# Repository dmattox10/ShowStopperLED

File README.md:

# ShowStopperLED
A five channel LED strip lighting Controller with serious audio reactivity and many display modes

The Android app communicates over Bluetooth 2.1 with the board, setting modes, and individual settings for each mode.
There is an audio input, which I was really impressed with myself for, because it introduced ZERO noise at all! The audio modes were my absolute favorite.

I stopped working on this project 7 years ago. I got mine working, as well as one for a friend, but a week after I got my prototypes in the mail and assembled them, the competitor released pretty much the same thing, ready for sale, and I gave up.

There are many different iterations, most untested, but the "defiance" version was built, and used successfully, including a $500 traffic ticket because I didn't realize it was on, and it was flashing "Red-Red", "Blue-Blue" on my car, and I got pulled over.

# An Apology: This was all completed and over, before I ever learned about Git!

## Android:
I've included every copy of the source code I have found in my old backups, I didn't compile and test any at this point, since I've switched to iOS personally, and don't have any Android devices lying around. I didn't use or have any apple equipment when I started the project.

## Boards:
I've included every version I made a board for, again, only "defiance" was produced in quantity and tested thoroughly.

## Arduino:
I started with an ATmega328P, moved to a PJRC Teensy 2.0, the code is a mess of files, and I can't tell which one is the "latest" version. The longest iterations are over 2k lines, pretty well commented.

## Media:
All of the files in this directory are photos of the equipment or advertising materials I came up with.

## Demo Links:
I recorded two videos with one of my best friends, of the ShowStopper working, on my 1993 Dodge Stealth.
- [Audio Modes](https://www.youtube.com/watch?v=f9GeiqDAIMo)
- [Motion Modes](https://www.youtube.com/watch?v=yMCRMerskfM)

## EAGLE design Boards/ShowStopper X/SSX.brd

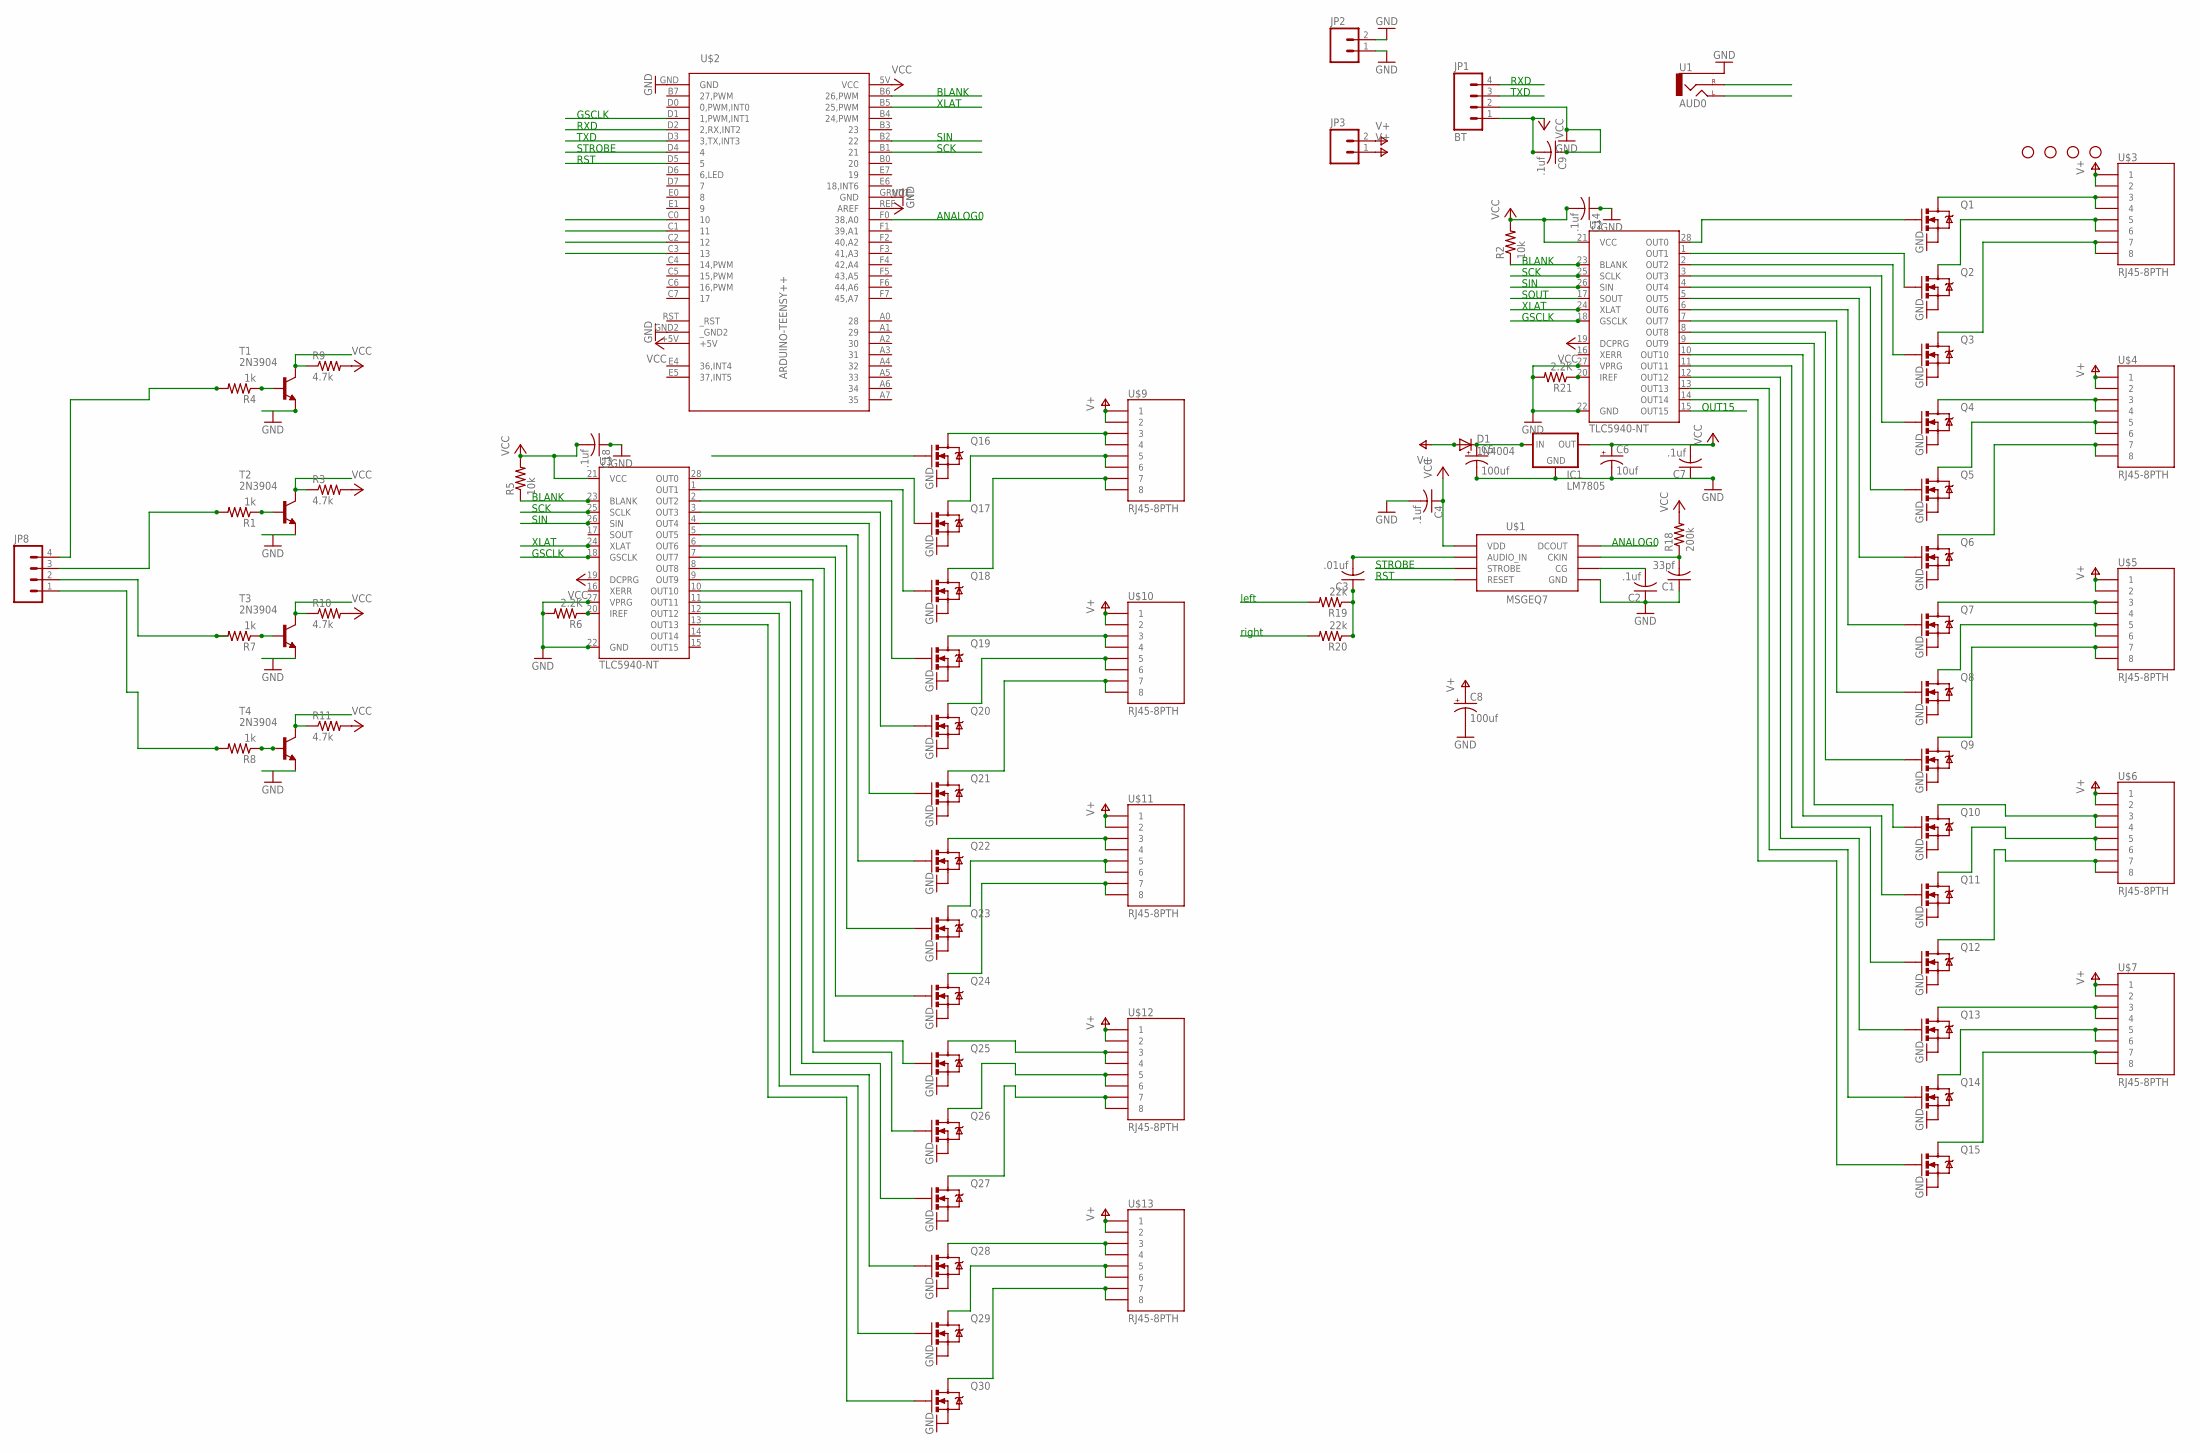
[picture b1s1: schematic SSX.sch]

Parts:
C1: 33pf; C025-025X050
C2, C4, C7, C9, C14, C18: .1uf; C025-025X050
C3: .01uf; C025-025X050
C5, C8: 100uf; CPOL-RADIAL-100UF-25V
C6: 10uf; CPOL-RADIAL-10UF-25V
D1: 1N4004; DIODE-1N4001
IC1: LM7805; TO220-IGO
JP1: BT; 1X04_LOCK
JP2, JP3: M025MM; SCREWTERMINAL-5MM-2
JP4, JP5, JP6, JP7: STAND-OFF
JP8: M04PTH; 1X04
Q1, Q2, Q3, Q4, Q5, Q6, Q7, Q8, Q9, Q10, Q11, Q12, Q13, Q14, Q15, Q16, Q17, Q18, Q19, Q20, Q21, Q22, Q23, Q24, Q25, Q26, Q27, Q28, Q29, Q30: MOSFET-NCHANNELPTH2; TO220V
R1, R4, R7, R8: 1k; 0207/2V
R2, R5: 10k; 0207/2V
R3, R9, R10, R11: 4.7k; 0207/2V
R6, R21: 2.2K; 0207/2V
R18: 200k; 0207/2V
R19, R20: 22k; 0207/2V
T1, T2, T3, T4: 2N3904; TO92
U1: AUD0; AUDIO-JACK
U2, U3: TLC5940-NT; DIL28-3
U$1: MSGEQ7_PTH; DIL08
U$2: ARDUINO-TEENSY++; TEENSY++
U$3, U$4, U$5, U$6, U$7, U$9, U$10, U$11, U$12, U$13: RJ45-8PTH; RJ45-8

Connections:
ANALOG0: U$1.3 (DCOUT), U$2.F0 (38,A0)
ARS: U$1.7 (RESET), U$2.D5 (5)
BL: R10.1, T3.1 (C), U$2.C1 (11)
BLANK: R2.1, U2.23 (BLANK), U$2.B6 (26,PWM)
BLANK1: R5.1, U3.23 (BLANK)
GND: C1.1, C2.1, C4.2, C5.2 (-), C6.2 (-), C7.1, C8.2 (-), C9.1, C14.1, C18.1, IC1.GND, JP1.2, JP2.1, JP2.2, Q1.3 (S), Q2.3 (S), Q3.3 (S), Q4.3 (S), Q5.3 (S), Q6.3 (S), Q7.3 (S), Q8.3 (S), Q9.3 (S), Q10.3 (S), Q11.3 (S), Q12.3 (S), Q13.3 (S), Q14.3 (S), Q15.3 (S), Q16.3 (S), Q17.3 (S), Q18.3 (S), Q19.3 (S), Q20.3 (S), Q21.3 (S), Q22.3 (S), Q23.3 (S), Q24.3 (S), Q25.3 (S), Q26.3 (S), Q27.3 (S), Q28.3 (S), Q29.3 (S), Q30.3 (S), R6.2, R21.2, U1.SLEEVE, U2.22 (GND), U2.27 (VPRG), U3.22 (GND), U3.27 (VPRG), U$1.2 (GND), U$2.GND, U$2.GND2 (_GND2), U$2.GRND1 (GND)
GSCLK: U2.18 (GSCLK), U$2.D1 (1,PWM,INT1)
GSCLK1: U3.18 (GSCLK)
HL: R11.1, T4.1 (C), U$2.C0 (10)
LEFT: R19.2, U1.TIP (LEFT)
LTS: R3.1, T2.1 (C), U$2.C2 (12)
unnamed: Q7.2 (D), U$5.3, U$5.4
unnamed: Q2.2 (D), U$3.5, U$3.6
unnamed: Q3.2 (D), U$3.7, U$3.8
unnamed: Q10.2 (D), U$6.3, U$6.4
unnamed: Q9.1 (G), U2.8 (OUT8)
unnamed: Q2.1 (G), U2.1 (OUT1)
unnamed: Q3.1 (G), U2.2 (OUT2)
unnamed: Q4.1 (G), U2.3 (OUT3)
unnamed: Q5.2 (D), U$4.5, U$4.6
unnamed: Q5.1 (G), U2.4 (OUT4)
unnamed: Q6.1 (G), U2.5 (OUT5)
unnamed: Q7.1 (G), U2.6 (OUT6)
unnamed: Q8.1 (G), U2.7 (OUT7)
unnamed: Q17.1 (G), U3.28 (OUT0)
unnamed: Q10.1 (G), U2.9 (OUT9)
unnamed: Q11.1 (G), U2.10 (OUT10)
unnamed: Q12.1 (G), U2.11 (OUT11)
unnamed: Q13.1 (G), U2.12 (OUT12)
unnamed: Q14.1 (G), U2.13 (OUT13)
unnamed: Q15.1 (G), U2.14 (OUT14)
unnamed: Q6.2 (D), U$4.7, U$4.8
unnamed: Q13.2 (D), U$7.3, U$7.4
unnamed: Q8.2 (D), U$5.5, U$5.6
unnamed: C1.2, R18.1, U$1.8 (CKIN)
unnamed: Q9.2 (D), U$5.7, U$5.8
unnamed: Q14.2 (D), U$7.5, U$7.6
unnamed: Q11.2 (D), U$6.5, U$6.6
unnamed: C3.2, U$1.5 (AUDIO_IN)
unnamed: Q12.2 (D), U$6.7, U$6.8
unnamed: Q15.2 (D), U$7.7, U$7.8
unnamed: Q1.2 (D), U$3.3, U$3.4
unnamed: C2.2, U$1.6 (CG)
unnamed: Q4.2 (D), U$4.3, U$4.4
unnamed: Q1.1 (G), U2.28 (OUT0)
unnamed: R21.1, U2.20 (IREF)
unnamed: C3.1, R19.1, R20.1
unnamed: Q18.1 (G), U3.1 (OUT1)
unnamed: Q19.1 (G), U3.2 (OUT2)
unnamed: Q20.1 (G), U3.3 (OUT3)
unnamed: C5.1 (+), D1.C, IC1.IN
unnamed: Q21.1 (G), U3.4 (OUT4)
unnamed: Q22.1 (G), U3.5 (OUT5)
unnamed: Q23.1 (G), U3.6 (OUT6)
unnamed: Q25.1 (G), U3.8 (OUT8)
unnamed: Q26.1 (G), U3.9 (OUT9)
unnamed: Q27.1 (G), U3.10 (OUT10)
unnamed: Q28.1 (G), U3.11 (OUT11)
unnamed: Q29.1 (G), U3.12 (OUT12)
unnamed: Q30.1 (G), U3.13 (OUT13)
unnamed: R1.1, T2.2 (B)
unnamed: Q17.2 (D), U$9.5, U$9.6
unnamed: Q18.2 (D), U$9.7, U$9.8
unnamed: Q20.2 (D), U$10.5, U$10.6
unnamed: Q21.2 (D), U$10.7, U$10.8
unnamed: Q23.2 (D), U$11.5, U$11.6
unnamed: Q24.2 (D), U$11.7, U$11.8
unnamed: Q26.2 (D), U$12.5, U$12.6
unnamed: Q27.2 (D), U$12.7, U$12.8
unnamed: Q16.2 (D), U$9.3, U$9.4
unnamed: Q19.2 (D), U$10.3, U$10.4
unnamed: Q22.2 (D), U$11.3, U$11.4
unnamed: Q25.2 (D), U$12.3, U$12.4
unnamed: Q28.2 (D), U$13.3, U$13.4
unnamed: Q29.2 (D), U$13.5, U$13.6
unnamed: Q30.2 (D), U$13.7, U$13.8
unnamed: R4.1, T1.2 (B)
unnamed: Q24.1 (G), U3.7 (OUT7)
unnamed: R6.1, U3.20 (IREF)
unnamed: R7.1, T3.2 (B)
unnamed: R8.1, T4.2 (B)
unnamed: JP8.4, R4.2
unnamed: JP8.3, R1.2
unnamed: JP8.2, R7.2
unnamed: JP8.1, R8.2
OUT15: Q16.1 (G), U2.15 (OUT15)
RIGHT: R20.2, U1.RING (RIGHT)
RTS: R9.1, T1.1 (C), U$2.C3 (13)
RXD: JP1.4, U$2.D3 (3,TX,INT3)
SCK: U2.25 (SCLK), U$2.B1 (21)
SCK1: U3.25 (SCLK)
SIN: U2.26 (SIN), U$2.B2 (22)
SOUT: U2.17 (SOUT), U3.26 (SIN)
STROBE: U$1.4 (STROBE), U$2.D4 (4)
TXD: JP1.3, U$2.D2 (2,RX,INT2)
V+: C8.1 (+), D1.A, JP3.1, JP3.2, U$3.1, U$3.2, U$4.1, U$4.2, U$5.1, U$5.2, U$6.1, U$6.2, U$7.1, U$7.2, U$9.1, U$9.2, U$10.1, U$10.2, U$11.1, U$11.2, U$12.1, U$12.2, U$13.1, U$13.2
VCC: C4.1, C6.1 (+), C7.2, C9.2, C14.2, C18.2, IC1.OUT, JP1.1, R2.2, R3.2, R5.2, R9.2, R10.2, R11.2, R18.2, U2.19 (DCPRG), U2.21 (VCC), U3.19 (DCPRG), U3.21 (VCC), U$1.1 (VDD), U$2.5V (VCC), U$2.+5V, U$2.REF (AREF)
XLAT: U2.24 (XLAT), U$2.B5 (25,PWM)
XLAT1: U3.24 (XLAT)

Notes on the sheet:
ANALOG0
RST
STROBE
left
right
SIN
SCK
XLAT
BLANK
GSCLK
RXD
TXD
SOUT
OUT15

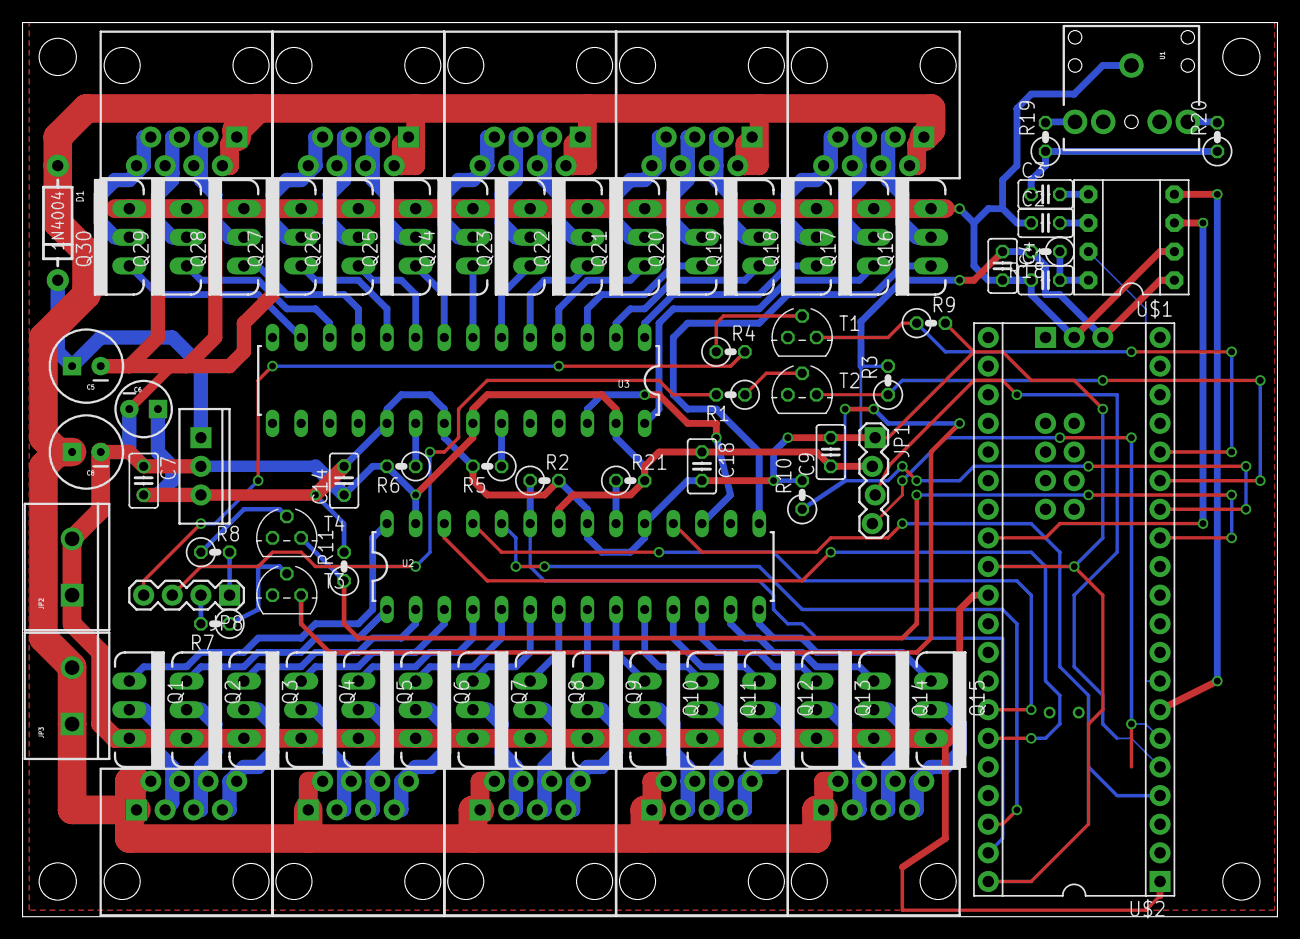
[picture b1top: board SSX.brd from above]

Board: 2 copper layers, 111.3 x 79.3 mm, 85 parts (0 on the bottom side), 96 nets.

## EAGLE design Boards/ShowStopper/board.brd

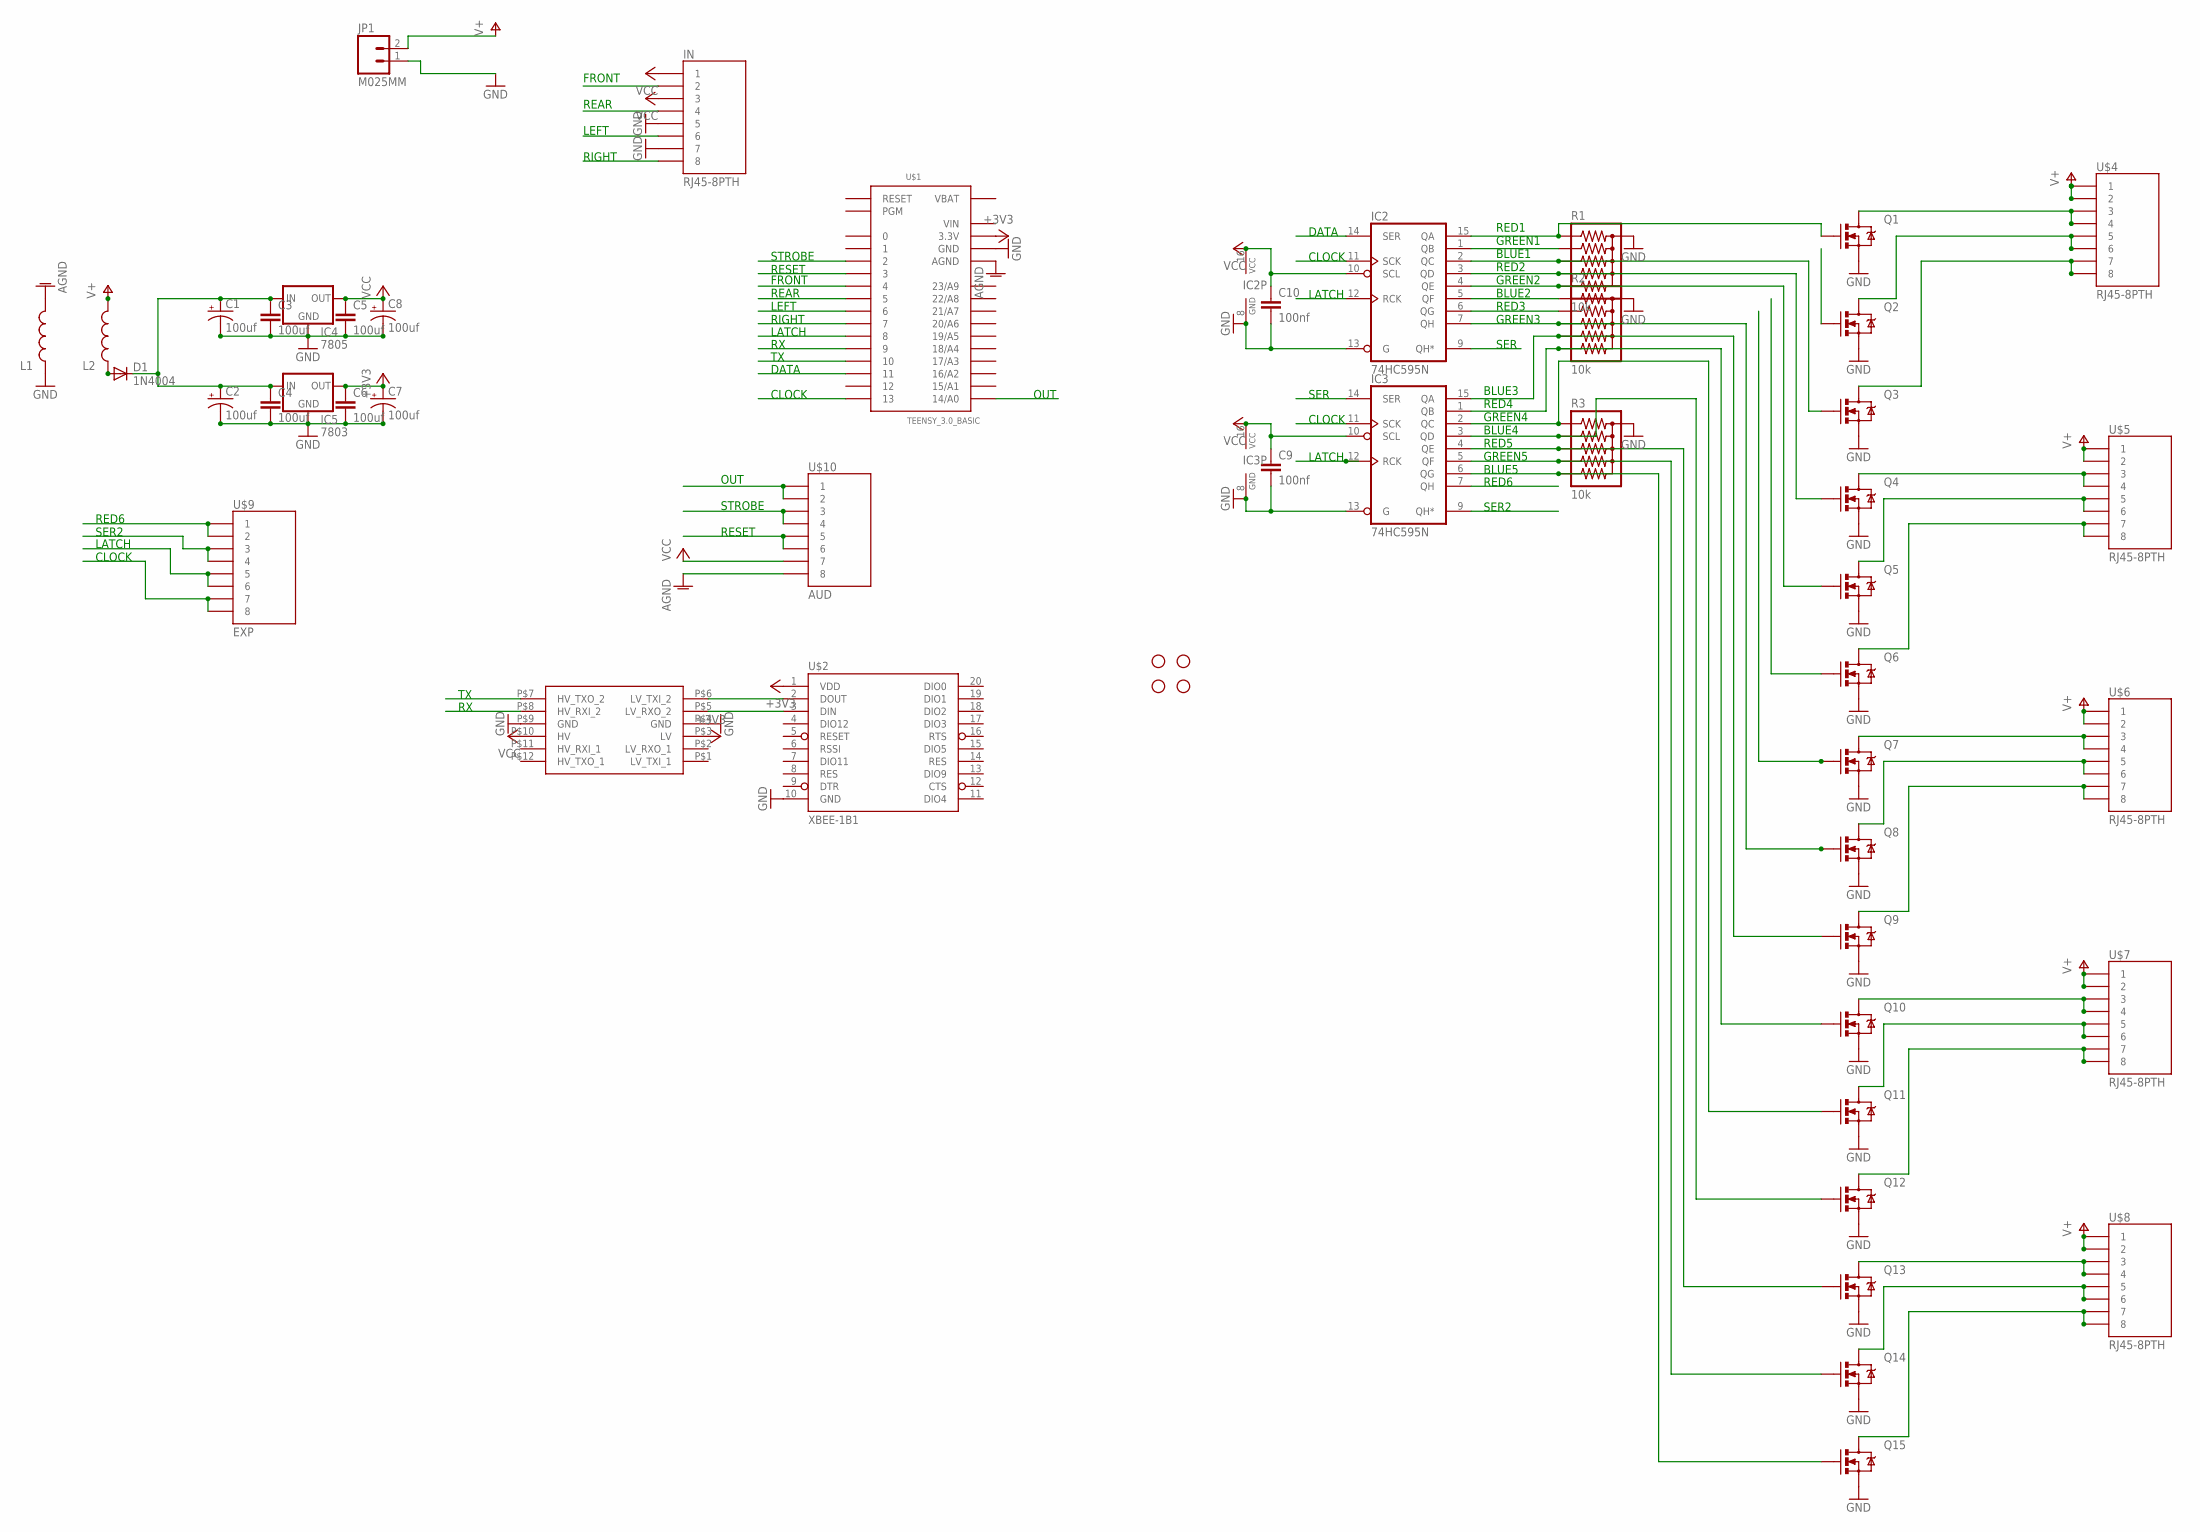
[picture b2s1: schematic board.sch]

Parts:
C1, C2, C7, C8: 100uf; CPOL-RADIAL-100UF-25V
C3, C4, C5, C6: 100uf; CAP-PTH-SMALL
C9, C10: 100nf; CAP-PTH-SMALL
D1: 1N4004; DO41-10
IC2, IC3: 74HC595N; DIL16
IC4: 7805; TO220-IGO
IC5: 7803; 78XXL
IN: RJ45-8PTH; RJ45-8
JP1: M025MM; SCREWTERMINAL-5MM-2
L1, L2: INDUCTORRLB0912; RLB0912
Q1, Q2, Q3, Q4, Q5, Q6, Q7, Q8, Q9, Q10, Q11, Q12, Q13, Q14, Q15: MOSFET-NCHANNELFQP30N06L; TO220V
R1, R2, R3: 10k; RPACK-SIP-PTH-5
STANDOFF1, STANDOFF2, STANDOFF3, STANDOFF4: STAND-OFF
U$1: TEENSY_3.0_BASIC
U$2: XBEE-1B1; XBEE-1
U$3: LOGIC_LEVEL_CONVERTER
U$4, U$5, U$6, U$7, U$8: RJ45-8PTH; RJ45-8
U$9: EXP; RJ45-8
U$10: AUD; RJ45-8

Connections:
+3V3: C6.1, C7.1 (+), IC5.GND (OUT), U$1.3.3V, U$1.3.3V1 (3.3V), U$2.1 (VDD), U$3.P$3 (LV)
AGND: L1.2, U$1.AGND, U$10.8
BLUE1: IC2.2 (QC), Q3.1 (G), R1.P$4 (4)
BLUE2: IC2.5 (QF), Q6.1 (G), R2.P$2 (2)
BLUE3: IC3.15 (QA), Q9.1 (G), R2.P$5 (5)
BLUE4: IC3.3 (QD), Q12.1 (G), R3.P$3 (3)
BLUE5: IC3.6 (QG), Q15.1 (G), R3.P$6 (6)
CLOCK: IC2.11 (SCK), IC3.11 (SCK), U$1.13, U$9.7, U$9.8
DATA: IC2.14 (SER), U$1.11
FRONT: IN.2, U$1.4
GND: C1.2 (-), C2.2 (-), C3.2, C4.2, C5.2, C6.2, C7.2 (-), C8.2 (-), C9.2, C10.2, IC2.8 (GND), IC2.13 (G), IC3.8 (GND), IC3.13 (G), IC4.GND, IC5.IN (GND), IN.5, IN.7, JP1.1, L1.1, Q1.3 (S), Q2.3 (S), Q3.3 (S), Q4.3 (S), Q5.3 (S), Q6.3 (S), Q7.3 (S), Q8.3 (S), Q9.3 (S), Q10.3 (S), Q11.3 (S), Q12.3 (S), Q13.3 (S), Q14.3 (S), Q15.3 (S), R1.P$1 (1), R2.P$1 (1), R3.P$1 (1), U$1.GND, U$1.GND1 (GND), U$2.10 (GND), U$3.P$4 (GND), U$3.P$9 (GND)
GREEN1: IC2.1 (QB), Q2.1 (G), R1.P$3 (3)
GREEN2: IC2.4 (QE), Q5.1 (G), R1.P$6 (6)
GREEN3: IC2.7 (QH), Q8.1 (G), R2.P$4 (4)
GREEN4: IC3.2 (QC), Q11.1 (G), R3.P$2 (2)
GREEN5: IC3.5 (QF), Q14.1 (G), R3.P$5 (5)
LATCH: IC2.12 (RCK), IC3.12 (RCK), U$1.8, U$9.5, U$9.6
LEFT: IN.6, U$1.6
unnamed: Q3.2 (D), U$4.7, U$4.8
unnamed: D1.A, L2.1
unnamed: Q4.2 (D), U$5.3, U$5.4
unnamed: Q5.2 (D), U$5.5, U$5.6
unnamed: Q6.2 (D), U$5.7, U$5.8
unnamed: C1.1 (+), C2.1 (+), C3.1, C4.1, D1.C, IC4.IN, IC5.OUT (IN)
unnamed: Q7.2 (D), U$6.3, U$6.4
unnamed: Q8.2 (D), U$6.5, U$6.6
unnamed: Q9.2 (D), U$6.7, U$6.8
unnamed: Q10.2 (D), U$7.3, U$7.4
unnamed: Q11.2 (D), U$7.5, U$7.6
unnamed: Q12.2 (D), U$7.7, U$7.8
unnamed: Q13.2 (D), U$8.3, U$8.4
unnamed: Q14.2 (D), U$8.5, U$8.6
unnamed: Q15.2 (D), U$8.7, U$8.8
unnamed: Q1.2 (D), U$4.3, U$4.4
unnamed: Q2.2 (D), U$4.5, U$4.6
unnamed: U$2.3 (DIN), U$3.P$5 (LV_RXO_2)
unnamed: U$2.2 (DOUT), U$3.P$6 (LV_TXI_2)
OUT: U$1.14/A0, U$10.1, U$10.2
REAR: IN.4, U$1.5
RED1: IC2.15 (QA), Q1.1 (G), R1.P$2 (2)
RED2: IC2.3 (QD), Q4.1 (G), R1.P$5 (5)
RED3: IC2.6 (QG), Q7.1 (G), R2.P$3 (3)
RED4: IC3.1 (QB), Q10.1 (G), R2.P$6 (6)
RED5: IC3.4 (QE), Q13.1 (G), R3.P$4 (4)
RED6: IC3.7 (QH), U$9.1, U$9.2
RESET: U$1.3, U$10.5, U$10.6
RIGHT: IN.8, U$1.7
RX: U$1.9, U$3.P$7 (HV_TXO_2)
SER: IC2.9 (QH*), IC3.14 (SER)
SER2: IC3.9 (QH*), U$9.3, U$9.4
STROBE: U$1.2, U$10.3, U$10.4
TX: U$1.10, U$3.P$8 (HV_RXI_2)
V+: JP1.2, L2.2, U$4.1, U$4.2, U$5.1, U$5.2, U$6.1, U$6.2, U$7.1, U$7.2, U$8.1, U$8.2
VBAT: U$1.VBAT
VCC: C5.1, C8.1 (+), C9.1, C10.1, IC2.10 (SCL), IC2.16 (VCC), IC3.10 (SCL), IC3.16 (VCC), IC4.OUT, IN.1, IN.3, U$3.P$10 (HV), U$10.7
VIN: U$1.VIN

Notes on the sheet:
RED1 GREEN1 BLUE1 RED2 GREEN2 BLUE2 RED3 GREEN3
BLUE3 RED4 GREEN4 BLUE4 RED5 GREEN5 BLUE5
DATA
CLOCK
LATCH
SER
STROBE RESET
OUT
RED6
SER2
RED6 SER2
FRONT REAR LEFT RIGHT
LATCH CLOCK
OUT STROBE RESET
FRONT REAR LEFT RIGHT

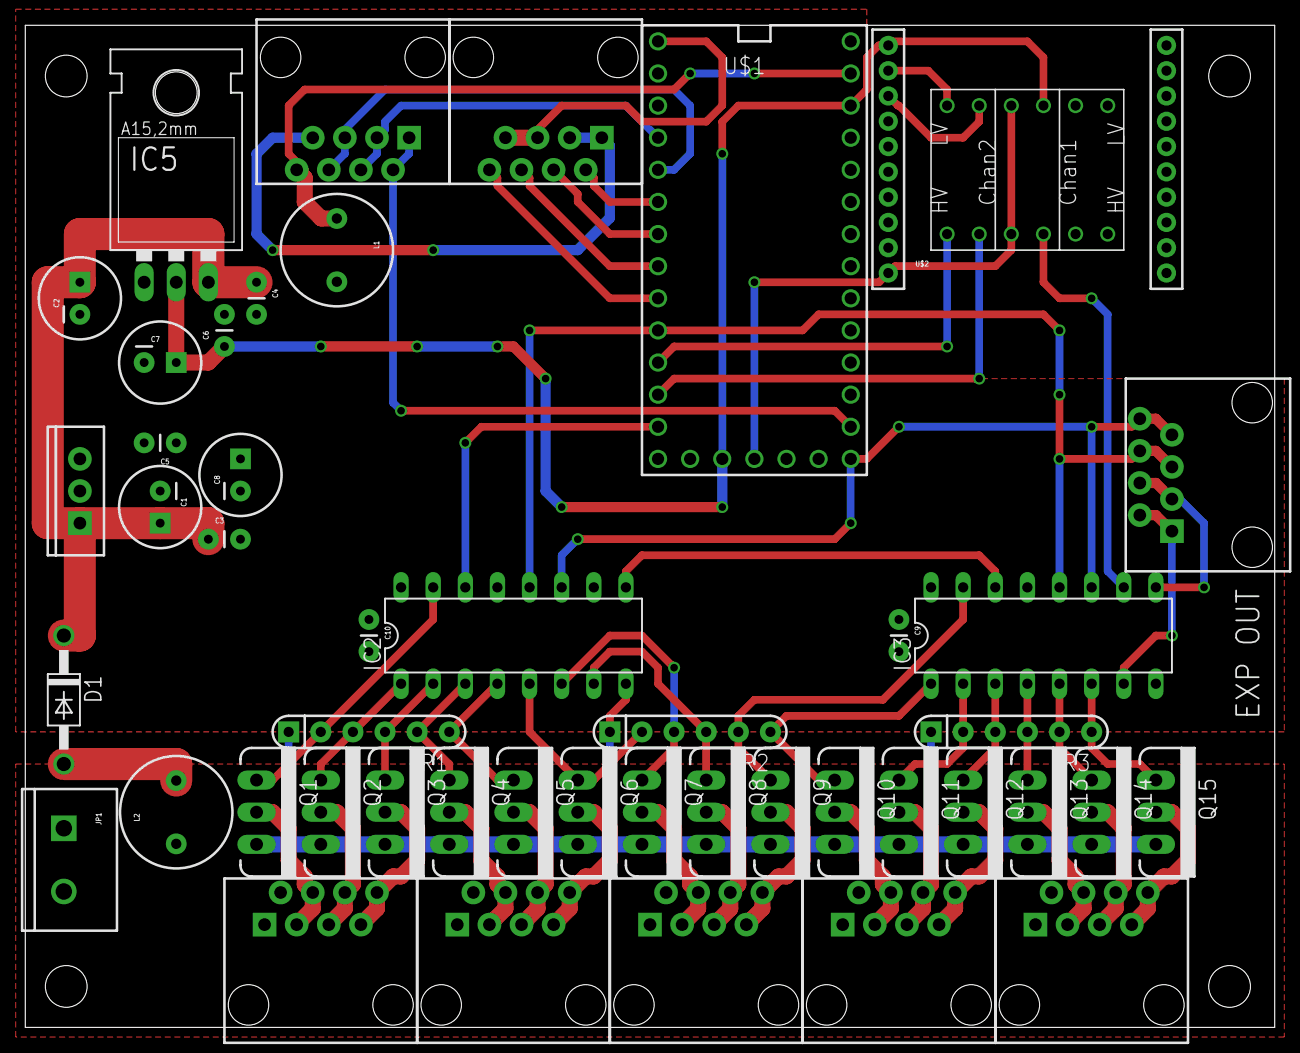
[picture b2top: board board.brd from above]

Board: 2 copper layers, 98.8 x 79.2 mm, 51 parts (0 on the bottom side), 54 nets.

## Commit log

2020-10-20 Should be it
2020-10-20 Edited README

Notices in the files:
parts and their libraries:
SparkFun-Connectors: Licensing: CC v3.0 Share-Alike You are welcome to use this library for commercial purposes.
tpp: Licensed Under Creative Commons Attribution-ShareAlike 3.0 Unported (CC BY-SA 3.0)
